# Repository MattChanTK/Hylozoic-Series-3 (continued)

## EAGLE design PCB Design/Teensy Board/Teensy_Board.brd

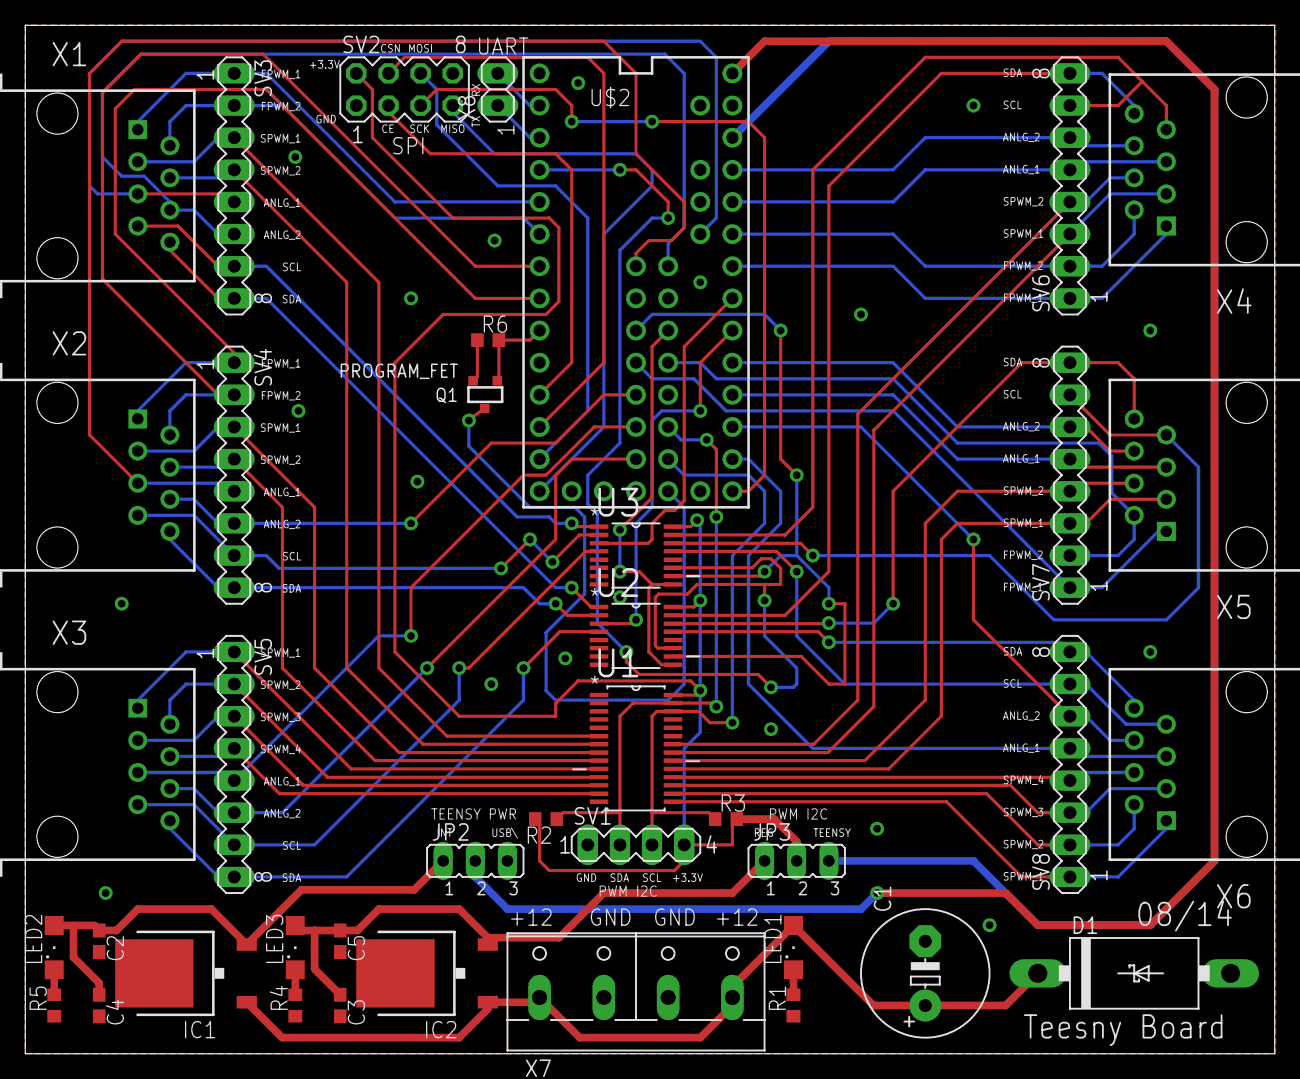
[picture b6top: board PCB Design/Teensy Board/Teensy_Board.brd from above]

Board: 2 copper layers, 98.7 x 81.3 mm, 40 parts (0 on the bottom side), 74 nets.

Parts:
C1: 470uF; E5-10,5
C2, C3: 1uF; C0603
C4, C5: 100nF; C0603
D1: SB540E-G; DO201T15
IC1: MC7805BDTRKG; DPACK_3
IC2: UA78M33CKVU; DPACK
JP2, JP3: JP2
LED1, LED2, LED3: SML1206
Q1: PROGRAM_FET; SOT-23
R1, R4, R5: 470; R0603
R2, R3, R6: 4k7; R0603
SV1: PWM_I2C; MA04-1
SV2: SPI; MA04-2
SV3, SV4, SV5, SV6, SV7, SV8: MA08-1
U1: PCA9685PW; SOP65P640X110-28N
U2, U3: 74HC4051PW,118; SOP65P640X110-16N
U$2: TEENSY_3.1_ALL_PINS_AND_PADS; TEENSY_3.1_ALLPINS
X1, X2, X3, X4, X5, X6: RJ45-8X; RJ45-NO-SHIELD
X7: W237-4P
X8: UART; 1X02

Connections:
3V3INT: JP3.2, R2.2, R3.2, SV1.4, SV2.2, U1.28, U2.16, U3.16
+3V3: C3.1, C5.1, IC2.3, JP3.1, LED3.A
+5V: C2.1, C4.1, IC1.3, JP2.1, LED2.A
+12V: C1.+, D1.C, IC1.1, IC2.1, LED1.A, X7.1, X7.4
A0: SV8.5, U$2.14/A0, X6.5
A1: SV8.6, U$2.15/A1, X6.6
A2: SV7.5, U$2.16/A2, X5.5
A3: SV7.6, U$2.17/A3, X5.6
A8: SV6.5, U$2.22/A8, X4.5
A9: SV6.6, U$2.23/A9, X4.6
A11: SV3.5, U$2.A11, X1.5
A12: SV4.5, U$2.A12, X2.5
A13: SV3.6, U$2.A13, X1.6
A15: SV4.6, U$2.26, X2.6
A16: SV5.5, U$2.27, X3.5
A17: SV5.6, U$2.28, X3.6
CE: SV2.3, U$2.9
CSN: SV2.4, U$2.10
FPWM_1_1: SV3.1, U$2.3, X1.1
FPWM_1_2: SV3.2, U$2.4, X1.2
FPWM_2_1: SV4.1, U$2.6, X2.1
FPWM_2_2: SV4.2, U$2.5, X2.2
FPWM_4_1: SV6.1, U$2.20/A6, X4.1
FPWM_4_2: SV6.2, U$2.21/A7, X4.2
FPWM_5_1: SV7.1, U$2.25, X5.1
FPWM_5_2: SV7.2, U$2.32, X5.2
GND: C1.-, C2.2, C3.2, C4.2, C5.2, D1.A, IC1.4, IC2.2, Q1.2, R1.1, R4.1, R5.1, R6.1, SV1.1, SV2.1, U1.1, U1.2, U1.3, U1.4, U1.5, U1.14, U1.23, U1.24, U1.25, U2.6, U2.7, U2.8, U3.6, U3.7, U3.8, U$2.GND, U$2.GND1, U$2.GND2, X7.2, X7.3
MISO: SV2.7, U$2.12
MOSI: SV2.6, U$2.11
MUL_ADR_0: U2.11, U3.11, U$2.2
MUL_ADR_1: U2.10, U3.10, U$2.24
MUL_ADR_2: U2.9, U3.9, U$2.33
MUL_SCL: U3.3, U$2.19/A5
MUL_SCL_1: SV3.7, U3.1, X1.7
MUL_SCL_2: SV4.7, U3.2, X2.7
MUL_SCL_3: SV5.7, U3.4, X3.7
MUL_SCL_4: SV6.7, U3.15, X4.7
MUL_SCL_5: SV7.7, U3.14, X5.7
MUL_SCL_6: SV8.7, U3.13, X6.7
MUL_SDA: U2.3, U$2.18/A4
MUL_SDA_1: SV3.8, U2.1, X1.8
MUL_SDA_2: SV4.8, U2.2, X2.8
MUL_SDA_3: SV5.8, U2.4, X3.8
MUL_SDA_4: SV6.8, U2.15, X4.8
MUL_SDA_5: SV7.8, U2.14, X5.8
MUL_SDA_6: SV8.8, U2.13, X6.8
unnamed: LED1.C, R1.2
unnamed: LED3.C, R4.2
unnamed: LED2.C, R5.2
PGM: Q1.3, U$2.PGM
PGM_DO: Q1.1, R6.2, U$2.7
RX1: U$2.0, X8.2
SCK: SV2.5, U$2.13
SCL_PWM: R3.1, SV1.3, U1.26, U$2.29
SDA_PWM: R2.1, SV1.2, U1.27, U$2.30
SPWM_1_1: SV3.3, U1.6, X1.3
SPWM_1_2: SV3.4, U1.7, X1.4
SPWM_2_1: SV4.3, U1.8, X2.3
SPWM_2_2: SV4.4, U1.9, X2.4
SPWM_3_1: SV5.1, U1.10, X3.1
SPWM_3_2: SV5.2, U1.11, X3.2
SPWM_3_3: SV5.3, U1.12, X3.3
SPWM_3_4: SV5.4, U1.13, X3.4
SPWM_4_1: SV6.3, U1.21, X4.3
SPWM_4_2: SV6.4, U1.22, X4.4
SPWM_5_1: SV7.3, U1.19, X5.3
SPWM_5_2: SV7.4, U1.20, X5.4
SPWM_6_1: SV8.1, U1.15, X6.1
SPWM_6_2: SV8.2, U1.16, X6.2
SPWM_6_3: SV8.3, U1.17, X6.3
SPWM_6_4: SV8.4, U1.18, X6.4
TEENSY_3V3: JP3.3, U$2.3.3V, U$2.3.3V1, U$2.3.3V2
TEENSY_VIN: JP2.2, U$2.VIN
TX1: U$2.1, X8.1

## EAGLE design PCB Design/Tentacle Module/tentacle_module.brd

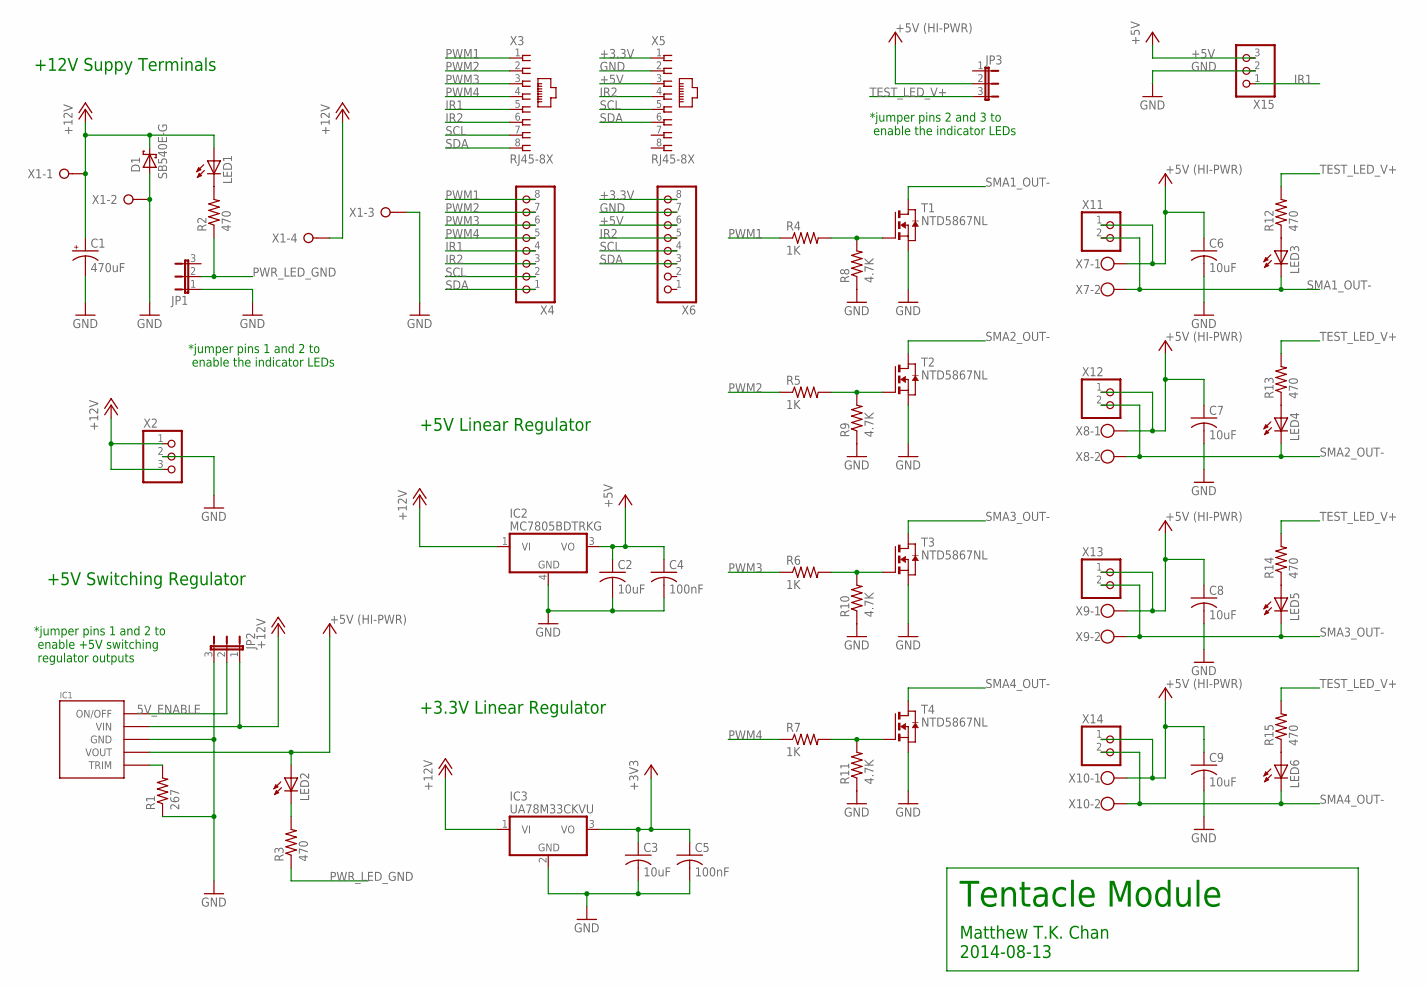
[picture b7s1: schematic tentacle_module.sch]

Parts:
C1: 470uF; E5-10,5
C2, C3, C6, C7, C8, C9: 10uF; C0603
C4, C5: 100nF; C0603
D1: SB540E-G; DO201T15
IC1: OKR-T/10-W12; OKR-C90
IC2: MC7805BDTRKG; DPACK_3
IC3: UA78M33CKVU; DPACK
JP1, JP2, JP3: JP2E; JP2
LED1, LED2, LED3, LED4, LED5, LED6: LEDSML1206; SML1206
R1: 267; R0603
R2, R3, R12, R13, R14, R15: 470; R0603
R4, R5, R6, R7: 1K; R0603
R8, R9, R10, R11: 4.7K; R0603
T1, T2, T3, T4: NTD5867NL; DPACK
X1: W237-04P; W237-4P
X2, X15: PINHD-1X3/90; 1X03/90
X3, X5: RJ45-8X; RJ45-NO-SHIELD
X4, X6: PINHD-1X8; 1X08
X7, X8, X9, X10: W237-102
X11, X12, X13, X14: PINHD-1X2/90; 1X02/90

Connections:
5V_ENABLE: IC1.ON/OFF, JP2.2
+3.3V: C3.1, C5.1, IC3.3 (VO), X5.1, X6.8
+5V: C2.1, C4.1, IC2.3 (VO), X5.3, X6.6, X15.3
+5V_HI-PWR: C6.1, C7.1, C8.1, C9.1, IC1.VOUT, JP3.2, LED2.A, X7.1, X8.1, X9.1, X10.1, X11.1, X12.1, X13.1, X14.1
+12V: C1.+, D1.C, IC1.VIN, IC2.1 (VI), IC3.1 (VI), JP2.1, LED1.A, X1.1, X1.4, X2.1, X2.3
GND: C1.-, C2.2, C3.2, C4.2, C5.2, C6.2, C7.2, C8.2, C9.2, D1.A, IC1.GND, IC2.4 (GND), IC3.2 (GND), JP1.1, JP2.3, R1.1, R8.1, R9.1, R10.1, R11.1, T1.3 (S), T2.3 (S), T3.3 (S), T4.3 (S), X1.2, X1.3, X2.2, X5.2, X6.7, X15.2
IR1: X3.5, X4.4, X15.1
IR2: X3.6, X4.3, X5.4, X6.5
unnamed: R5.2, R9.2, T2.1 (G)
unnamed: R6.2, R10.2, T3.1 (G)
unnamed: R7.2, R11.2, T4.1 (G)
unnamed: R4.2, R8.2, T1.1 (G)
unnamed: LED3.A, R12.1
unnamed: IC1.TRIM, R1.2
unnamed: LED2.C, R3.2
unnamed: LED1.C, R2.2
unnamed: LED4.A, R13.1
unnamed: LED5.A, R14.1
unnamed: LED6.A, R15.1
PWM1: R4.1, X3.1, X4.8
PWM2: R5.1, X3.2, X4.7
PWM3: R6.1, X3.3, X4.6
PWM4: R7.1, X3.4, X4.5
PWR_LED_GND: JP1.2, R2.1, R3.1
SCL: X3.7, X4.2, X5.5, X6.4
SDA: X3.8, X4.1, X5.6, X6.3
SMA1_OUT-: LED3.C, T1.2 (D), X7.2, X11.2
SMA2_OUT-: LED4.C, T2.2 (D), X8.2, X12.2
SMA3_OUT-: LED5.C, T3.2 (D), X9.2, X13.2
SMA4_OUT-: LED6.C, T4.2 (D), X10.2, X14.2
TEST_LED_V+: JP3.3, R12.2, R13.2, R14.2, R15.2

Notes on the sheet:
Tentacle Module
Matthew T.K. Chan 2014-08-13
+12V Suppy Terminals
*jumper pins 2 and 3 to enable the indicator LEDs
+5V Switching Regulator
*jumper pins 1 and 2 to enable the indicator LEDs
*jumper pins 1 and 2 to enable +5V switching regulator outputs
+5V Linear Regulator
+3.3V Linear Regulator

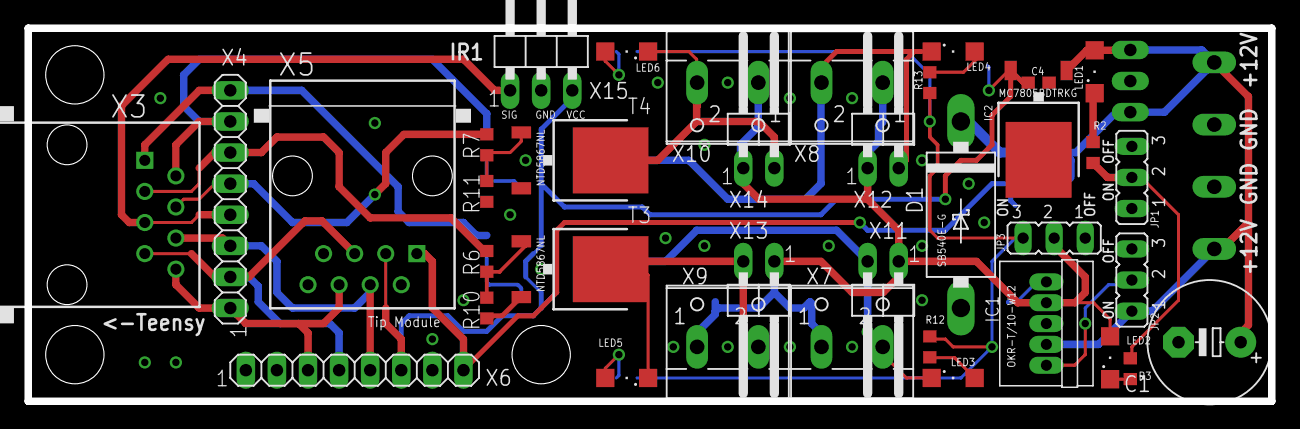
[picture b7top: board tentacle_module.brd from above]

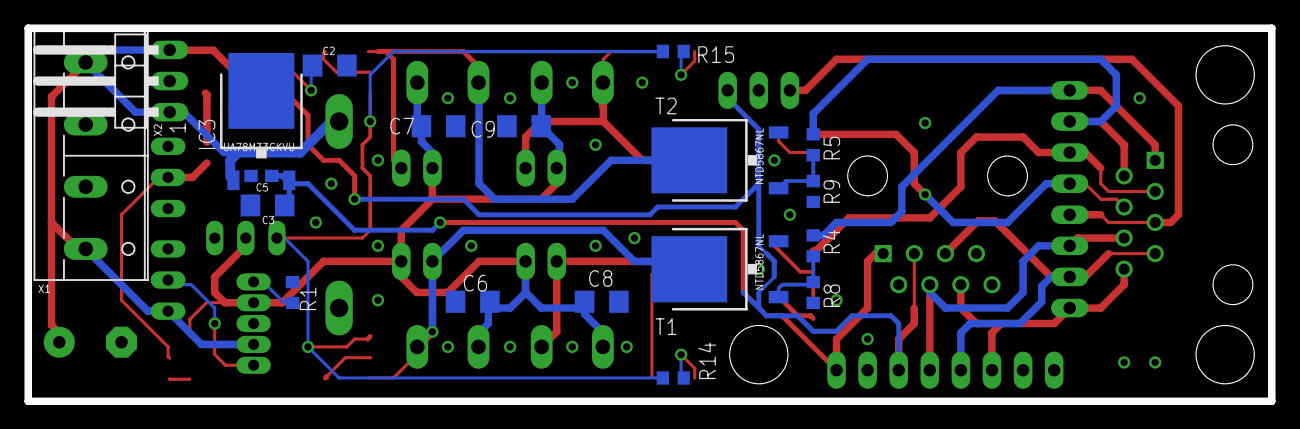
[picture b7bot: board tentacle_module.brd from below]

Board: 2 copper layers, 101.6 x 30.5 mm, 57 parts (19 on the bottom side), 31 nets.

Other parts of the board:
DRILEGEND: DRILEGEND

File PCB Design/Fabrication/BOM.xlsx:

Qty | Value | Device | Package | Parts | Description | Digikey Part # | Dipmicro Part #
3 |  | JP2E | JP2 | JP1, JP2, JP3 | JUMPER |  | DE1567, DE1562
6 |  | LEDSML1206 | SML1206 | LED1, LED2, LED3, LED4, LED5, LED6 | LED | 754-1171-1-ND
4 |  | PINHD-1X2/90 | 1X02/90 | X11, X12, X13, X14 | PIN HEADER | S5477-ND, S5456-ND | DE3851
2 |  | PINHD-1X3/90 | 1X03/90 | X2, X15 | PIN HEADER | S5478-ND, S5456-ND | DE3852
2 |  | PINHD-1X8 | 1X08 | X4, X6 | PIN HEADER | S5483-ND,S5456-ND | DE3853
1 |  | W237-04P | W237-4P | X1 | WAGO SREW CLAMP |  | DE1632
4 |  | W237-102 | W237-102 | X7, X8, X9, X10 | WAGO SCREW CLAMP |  | DE1632
2 | 100nF | C-USC0603 | C0603 | C4, C5 | CAPACITOR, American symbol | 1276-1012-1-ND
6 | 10uF | C-USC0603 | C0603 | C2, C3, C6, C7, C8, C9 | CAPACITOR, American symbol | 490-7198-1-ND
4 | 1K | R-US_R0603 | R0603 | R4, R5, R6, R7 | RESISTOR, American symbol | 311-1.0GRCT-ND
1 | 267 | R-US_R0603 | R0603 | R1 | RESISTOR, American symbol | P267DBCT-ND
4 | 4.7K | R-US_R0603 | R0603 | R8, R9, R10, R11 | RESISTOR, American symbol | 311-4.7KGRCT-ND
6 | 470 | R-US_R0603 | R0603 | R2, R3, R12, R13, R14, R15 | RESISTOR, American symbol | RHM470DCT-ND
1 | 470uF | CPOL-USE5-10.5 | E5-10,5 | C1 | POLARIZED CAPACITOR, American symbol | P15363TB-ND
1 | MC7805BDTRKG | MC7805BDTRKG | DPACK_3 | IC2 | 1A Positive Voltage Regulators | MC7805BDTGOS-ND
4 | NTD5867NL | NTD5867NLT4G | DPACK | T1, T2, T3, T4 | MOS FET | NTD5867NLT4GOSTR-ND
1 | OKR-T/10-W12 | OKR-T/10-W12 | OKR-C90 | IC1 | 5V/10A Murata POL DC/DC Converter
2 | RJ45-8X | RJ45-8X | RJ45-NO-SHIELD | X3, X5 | CORCOM Modular RJ Jacks No Shield | AE10380-ND, AE10396-ND
1 | SB540E-G | SB540E-G | DO201T15 | D1 | SCHOTTKY BARRIER RECTIFIER 3.0 AMPERES 20, 30, 40 VOLT | 641-1419-1-ND
1 | UA78M33CKVU | UA78M33CKVU | DPACK | IC3 | Linear Voltage Reg | 296-21208-1-ND

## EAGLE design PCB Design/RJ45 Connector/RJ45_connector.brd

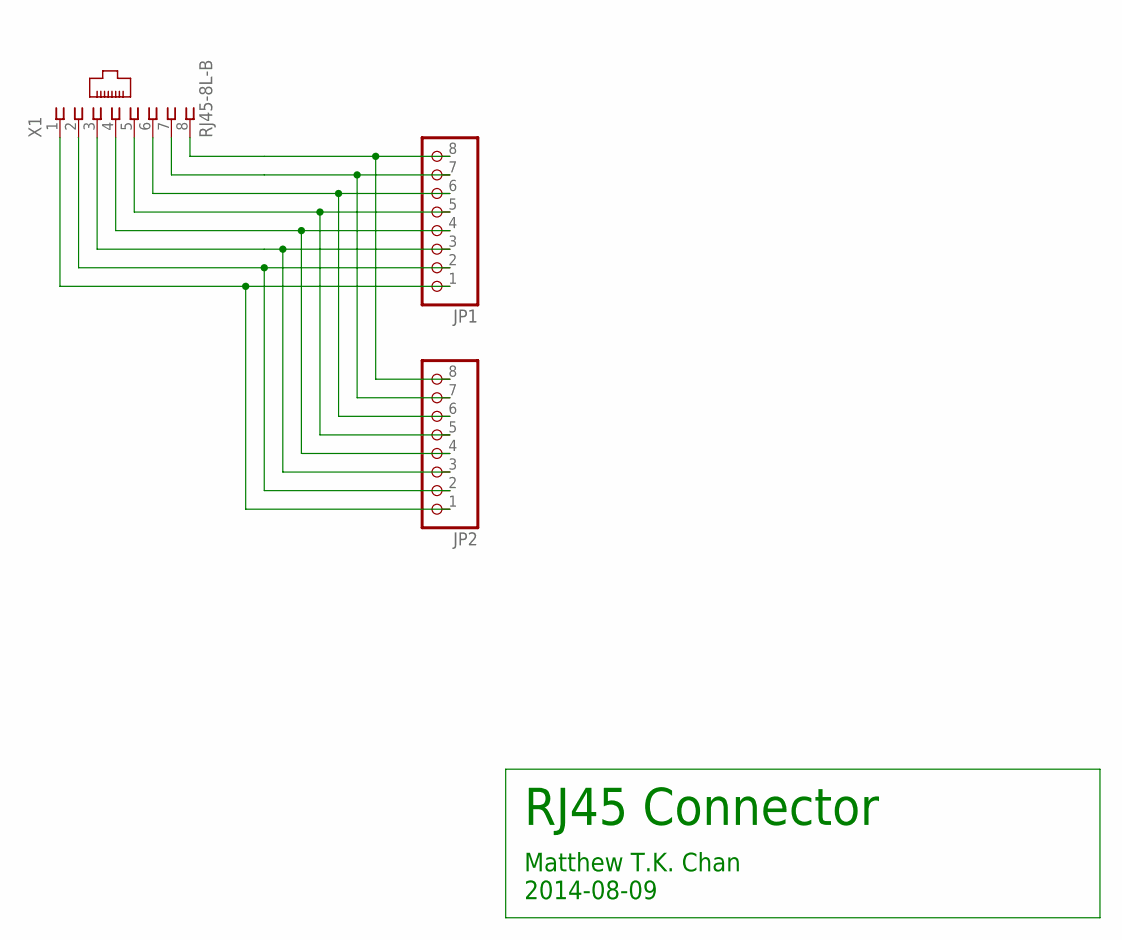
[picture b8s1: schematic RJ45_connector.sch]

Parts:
JP1, JP2: PINHD-1X8/90; 1X08/90
X1: RJ45-8L-B; RJ45-NO-SHIELD

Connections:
unnamed: JP1.8, JP2.8, X1.8
unnamed: JP1.7, JP2.7, X1.7
unnamed: JP1.6, JP2.6, X1.6
unnamed: JP1.5, JP2.5, X1.5
unnamed: JP1.4, JP2.4, X1.4
unnamed: JP1.3, JP2.3, X1.3
unnamed: JP1.2, JP2.2, X1.2
unnamed: JP1.1, JP2.1, X1.1

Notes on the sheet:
RJ45 Connector
Matthew T.K. Chan 2014-08-09

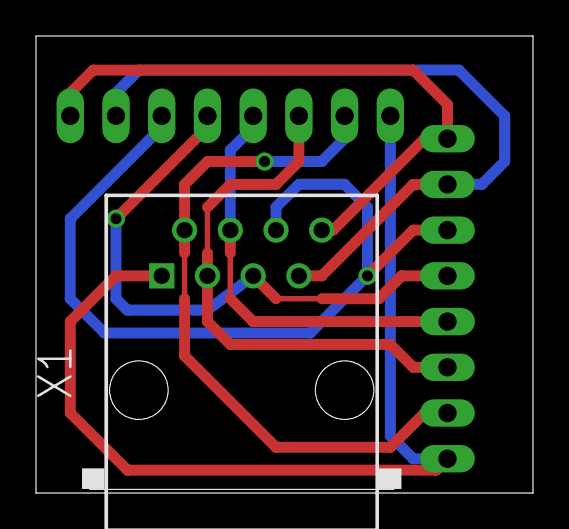
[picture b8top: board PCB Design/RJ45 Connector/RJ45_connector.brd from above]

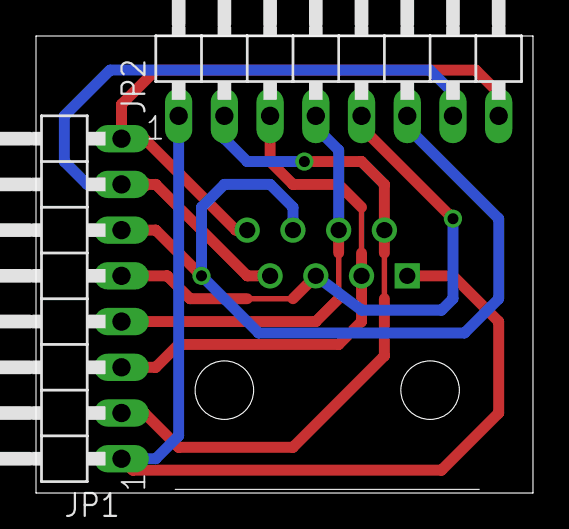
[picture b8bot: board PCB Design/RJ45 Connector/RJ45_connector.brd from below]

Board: 2 copper layers, 27.6 x 25.4 mm, 3 parts (2 on the bottom side), 8 nets.

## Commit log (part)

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2015-04-08 updating M0 and S0 in real-time (changed to Var variable) also outputing is_idle_mode and loop_time
2015-04-10 added install command for python34, and added a auto-start option to InteractiveCmd
2015-04-12 remove instantiate() from CBLA_node's init function
2015-04-15 added inactive behaviours. timeout after not receiving messages for a while
2015-04-16 made the output to the sma controller a squared value adjusted the constants accordingly allow modification of constant at the instantiation of the frond object
2015-04-17 change the T_model formula back to non-squared version as it actually works better added Protocell2 which is using a subclass of Simple node Implement Simple Node type nodes: Reflex Actuator, Half Fr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
2015-04-27 fixed bug that prevented custom configuration of wait_time adding plot model time stamp on sessions start and end save to file periodically
2015-04-27 change to a neat way to display multiple values on the gui
2015-04-27 plotting the data part of the model (work-in-progress)
2015-04-27 added sleep time to data_collect so that it doesn't slow down the whole system change the wait_time for the CBLA robot to limit to (minimum) 4 times the messenger's period
2015-04-28 added 3D plots tested for 1 LED and 1 ALS system
2015-04-28 set up for re-runing the experiment
2015-05-05 completed control and display frames for manual control
2015-05-05 moved old cbla code and processing gui code to archive (without the saved figures and pickle files)
2015-05-06 consolidated the gui functions for the prescripted behaviours and manual control to one file.
2015-05-06 rename non-code folders with a "_" in front of their folder anmes
2015-05-06 making sure that the cbla_engine uses relative path
2015-05-06 made custom_gui as its own package added way to import custom_gui when it's not already on the PYTHONPATH
2015-05-06 deleting unnecessary files
2015-05-07 deleted cbla's old gui test_behaviour remains using the basic gui provided by the abstract_node module
2015-05-07 separated custom_gui into multiple files
2015-05-07 remove the extra __construct_gui statement
2015-05-07 instantiating and caling the hmi from the main thread. (removed self.hmi) add "interactive-system" to the required package list for hmi_gui
2015-05-08 added .bat scripted need to the run the different modes
2015-05-08 remove the protocol for closing window to prevent the GUI from freezing upon termination.
2015-05-08 fixed the bug that it didn't actually use Var.val
2015-05-12 changed the list to a deque for faster operation when eliminating old data
2015-05-14 move the running average, and pseudodifferentiation to the abstract node module
2015-06-01 added and started editing the c++ Teensy firmware for the new layout.
2015-06-04 Tested new changes on all basic_behaviours
2015-06-04 Renamed the new layout as "Triplet"
2015-06-04 run all connected Teensy
2015-06-05 renamed cbla2 to cbla specified a 'spatial' mode removed defunct classes
2015-06-11 modified the cbla module's functions
2015-06-13 refactored the manual_control mode added the CBLA2_Manual and CBLA2_PRESCRIPTD modes
2015-06-13 modified the HMI to allow it to fit more data
2015-06-18 added data_collector to prescripted mode
2015-06-18 added 'random' mode to the CBLA behaviour
2015-06-23 implemented and tested the manual and prescripted mode for the CBLA_test_bed
2015-06-27 increase the max vibration intensity to 100
2015-06-27 added data collection with data collected every 1s to reduce impact on performance
2015-06-27 fixed bug: the communication for Light type hardcoded "2".
2015-06-28 sorting the prescripted mode's hmi by Teensyname
2015-06-29 renaming for the system_identification
2015-07-08 changed name to "Light Module"
2015-07-08 tested changing some of the parameter to figure out why it is so slow
2015-07-13 added data logger that uses the 'shelves' module status: seems to work, but need further testing and validation
2015-07-13 restored plotting functionality to prescripted version
2015-07-14 added get_packet function to return a specific packet in one of the session shelves
2015-07-14 removed the set filename for the log
2015-07-14 remove the original cbla's plotting module
2015-07-14 replace explict reference to the Class to an implicit
2015-07-14 reduce save_freq to 5.0s
2015-07-15 renaming idle 'reward' to 'value' first tuning of the spatial mode
2015-07-22 added that prevent training when there aren't enough samples region splitter removed unused classes; made the splitting a bit more efficient; also the scoring method for selecting best_cut is changed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
2015-07-28 using get block for the queue
2015-07-28 added "abstract_node." in front of the import statment
2015-07-28 reduce the number of candidate being considered changed from random choice to random uniform for cut value
2015-07-31 change some configuration parameters changed saving frequency to once every 60s
2015-08-01 fixed bug: the condition should be "and" not "or"
2015-08-04 remove splotting of the model
2015-08-05 limit the "avg_action_val" to a minimum of 0.0001 to prevent really large "val_inc simply because we got a small "avg_action_val"
2015-08-10 removed the unnecessary if-statement
2015-08-11 change 'spatial_node' to 'local_node' and est the scope to 'cbla_local'
2015-08-11 added 'Spatial...' which is same as 'Local...'
2015-08-12 using sum to link the different nodes
2015-08-15 moved location of robot's code changed some paramtere's value
2015-08-17 completed spatial local mode
2015-08-17 implemented globally randomly linked mode
2015-08-19 removed the now unnecessary local and spatical node sub-classes
2015-08-19 ignores pre-set s_range and uses an adaptive one.
2015-08-19 making initial learning step proportional to the dimensionality of its state-space
2015-08-25 added node and hmi for user study control purposes
2015-08-26 added beep sound every time it samples
2015-09-01 updated the BOM by highlighting the components we have in stock
2015-09-02 don't print the init_learning_done
2015-09-03 added more complete behaviour for the light node
2015-09-03 Integrated the switch_mode feature in the GUI Fixed a bug where S0 and M0 becomes initial value when restoring from previous sessions
2015-09-06 calculated the total_activation metric
2015-09-08 made the increment value a parameter
2015-09-11 stop trying to retrieve data when the session index points to nothing
2015-09-11 plotted the proximal_activation_array
2015-09-11 added automated sampling (now set to every 60s) to user_study node
2015-09-15 remove the the unnecessary code when executed as main
2015-09-17 added code that log input and output values during prescripted mode
2015-09-17 added reactor and updated code
2015-09-22 changed the code to grab random music files numbered from 1 to 50 .wav
2015-09-24 the adaptive activity mode starts even when init_learning is not done added those computed values to 'internal_state' for display purposes
2015-09-25 removed idle_mode entirely added a sigmoid function that maps relative action value to max range
2015-10-13 added outputs to UDP sockets
2015-10-13 fixed the guard block name
2015-10-15 completed the tested version of WashingtonCricketNode with test behaviour
2015-10-15 added the FinCricketNode
2015-10-16 Fixed a bug that caused the firmware to crash. NUM_FIN, NUM_CRICKET, NUMLIGHT needs to be scoped properly.
2015-10-16 added new sound module
2015-10-18 got I2C communication between SoundNode and SoundModule working
2015-10-18 modify to combine left and right channels
2015-10-18 working test behaviour
2015-10-18 updated the interactiove_system with some new features allowing it to be more modularized added code for USB communcation and defined communication protocol for cricket node.
2015-10-28 added behaviour codes for Washington
    t piu
2015-10-28 change the cricket_node's test behaviour to trigger 0, 1 with differnet ir sensors
2015-10-28 modified washing behaviour
2015-10-28 added the test teenst
2015-10-28 added manual control of fin, fin-cricket, and cricket nodes [NOT TESTED in REAL SCULPTURE]
2015-10-29 adding fall-bac code not tested yet
2015-11-03 added printout of the syste state
2015-11-16 remove output to socket from DataLogger
2015-11-16 added the hex file for the CBLA_Test_Bed firmware
2015-11-16 started on the node_spatial_map
2015-11-17 mapped "reference temperature" to a log to make the movement of the fin more visible
2015-11-17 fixed mistake in mapping reflex node
2015-11-20 added some code for building the spatial map though not being used yet.
2015-11-27 added incremental averaging with cap method for adapting m range
2015-11-30 commented out using linear_regression as model
2015-12-01 added ranges of inputs and outputs to the prescripted engine
2015-12-03 added more configurations that can be adjusted as arguments in the console
2015-12-04 printing more data to each CSV snapshot (included prescipted and each input and output nodes change default parameters
2015-12-08 added data analysis tool specifically for analyzing data from the user studies
2015-12-14 add the ability to accept either coordinate or node name as input to the get_displacement function
2015-12-17 added sound node to the prescritped code fixed one bug in the sound node's communicaiton protocol
2015-12-17 added some commented out codes
2015-12-17 added test teensy and correct serial numbers
2015-12-17 added the codes so that it only prints out the operation mode when it has changed
2015-12-17 added hex file for the FinCricket node
2015-12-18 added the Hex files that can be uploaded to the boards
2016-01-14 Started to add functionality to a test suite.
2016-01-15 Adding SerialCommand with the capability to print the compile date using the "VER" command. Does this break CBLA (or not, because CBLA is using HIDRaw)? Basic reformatting (prettifying) of the code.
2016-01-19 Added SerialCommand to sound modules.
2016-01-19 Fixed missing curly brace on if statement.
2016-01-19 Added specific code for the proximity sensor and automatic thresholding.
2016-01-19 Fixed the decaying property of the adaptive threshold, which was NOT SET
2016-01-20 Working sound level control using dacVolume. Less than about 0.75 is inaudible with the current setup.
2016-01-21 Add a number of additional SerialCommands (OPMODE to tell the operation mode of the Control Module) and some I2C handling code
2016-01-21 Added .gitignore file to repo
2016-01-22 Changes to the library and the project files to complete the merge
2016-01-22 Revert "Some edits to restore the functionality to before merging in the major reorganizational changes"
    This reverts commit b5d5aa4749c2ca7dfbae983437dfe0db3360e06f.
2016-01-22 Removed unnecessary code
2016-01-25 Started to create a folder for sensors and added the proximity sensor to this.
2016-01-26 Removed the redundant i2c files and moved the proximity sensor to the library
2016-01-26 consolidate all the core Python libraries into pyHylozoic3
2016-01-26 added ability to offset the plot; add special appearance setting for metric plots
2016-01-27 Added the ability to play synthesized sin wave
2016-01-28 changed back to fft 1024 and it doesn't crashed when communicating anymore
2016-01-28 Updated conf settings
2016-01-28 Files to help with creating documentation
2016-01-28 Some added documentation from Matt
2016-01-29 Updated installation docs
2016-01-29 added prerscripted reflex node
2016-02-01 added more documentations
2016-02-13 Fixed the bug that prevented the DataSaver's process from running.
    Turned out that the multiprocessing module requires the main module to be
    importable.
    Therefore, instead of using "if not main, then quit", but the main
    function in an "if main" statement.
2016-02-18 Added comments describing the TeensyManager, Teeensy Interface, and TeensyMonitor
2016-02-18 added description of the hardware folder in the README
2016-02-18 change backslash to forward slash
